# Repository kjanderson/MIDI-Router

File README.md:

# MIDI-Router
PIC24/FPGA code to route MIDI data on prototype hardware.

The objective of this project is to build a prototype that is able to route MIDI
signals from source to destination automatically.

The hardware provides 4 MIDI inputs, 4 MIDI thru's, and 4 MIDI outputs.
This software project implements the routing of the inputs to the outputs.

Notes
 - USB is copied from the MLA USB Framework
 - USB-app is copied from the application example in the MLA
 - USB-bsp is copied from the application example in the MLA

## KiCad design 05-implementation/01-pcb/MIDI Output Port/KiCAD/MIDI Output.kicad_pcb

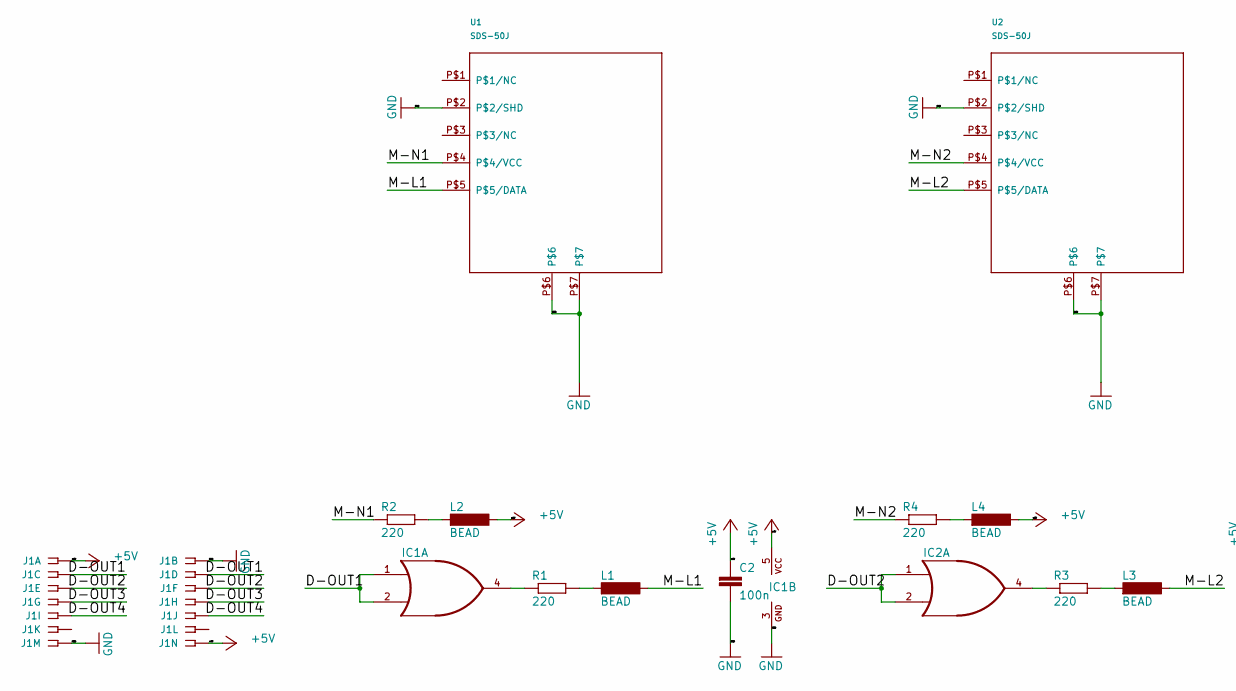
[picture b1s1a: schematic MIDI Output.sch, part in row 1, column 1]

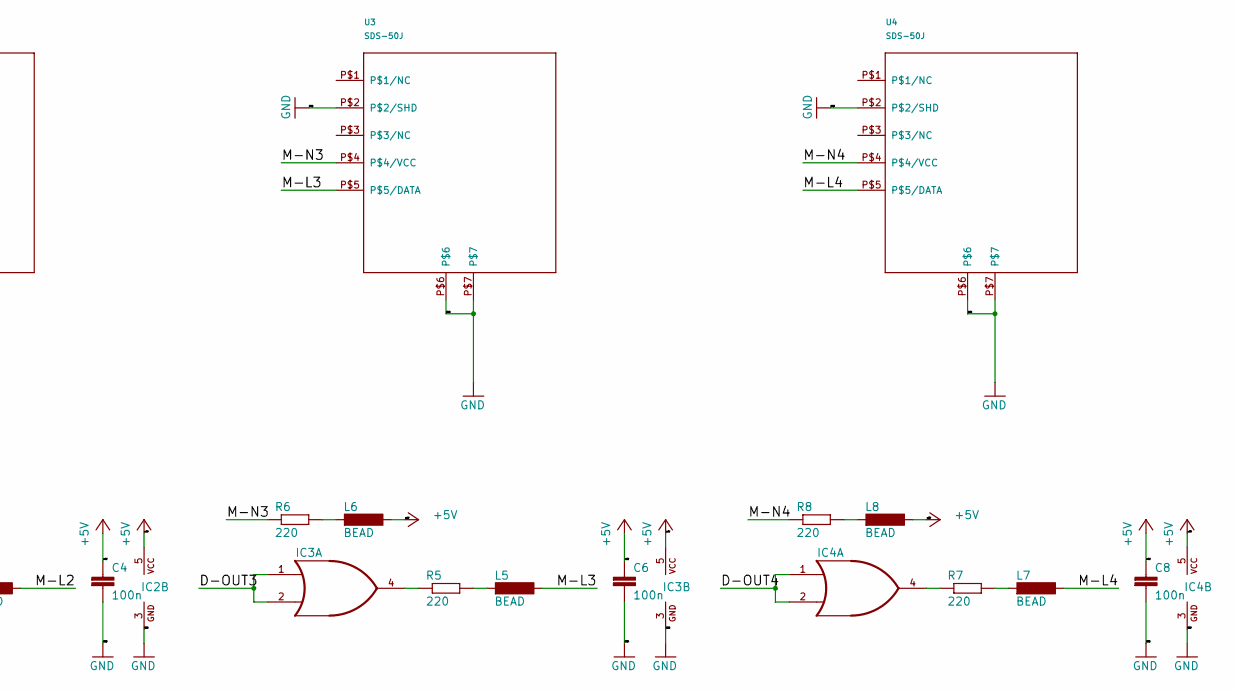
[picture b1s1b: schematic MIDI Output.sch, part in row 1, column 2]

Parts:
C2, C4, C6, C8: 100n; C0805
IC1, IC2, IC3, IC4: 741G32; SOT25
J1: SSW-107-02-G-D
L1, L2, L3, L4, L5, L6, L7, L8: BEAD; L0805
R1, R2, R3, R4, R5, R6, R7, R8: 220; R0805
U1, U2, U3, U4: SDS-50J

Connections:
+5V: C2.1, C4.1, C6.1, C8.1, IC1.5 (VCC), IC2.5 (VCC), IC3.5 (VCC), IC4.5 (VCC), J1.1, J1.14, L2.2, L4.2, L6.2, L8.2
/D-OUT1: IC1.1 (I0), IC1.2 (I1), J1.3, J1.4
/D-OUT2: IC2.1 (I0), IC2.2 (I1), J1.5, J1.6
/D-OUT3: IC3.1 (I0), IC3.2 (I1), J1.7, J1.8
/D-OUT4: IC4.1 (I0), IC4.2 (I1), J1.9, J1.10
/M-L1: L1.2, U1.P$5 (P$5/DATA)
/M-L2: L3.2, U2.P$5 (P$5/DATA)
/M-L3: L5.2, U3.P$5 (P$5/DATA)
/M-L4: L7.2, U4.P$5 (P$5/DATA)
/M-N1: R2.1, U1.P$4 (P$4/VCC)
/M-N2: R4.1, U2.P$4 (P$4/VCC)
/M-N3: R6.1, U3.P$4 (P$4/VCC)
/M-N4: R8.1, U4.P$4 (P$4/VCC)
GND: C2.2, C4.2, C6.2, C8.2, IC1.3 (GND), IC2.3 (GND), IC3.3 (GND), IC4.3 (GND), J1.2, J1.13, U1.P$2 (P$2/SHD), U1.P$6, U1.P$7, U2.P$2 (P$2/SHD), U2.P$6, U2.P$7, U3.P$2 (P$2/SHD), U3.P$6, U3.P$7, U4.P$2 (P$2/SHD), U4.P$6, U4.P$7
unnamed: IC1.4 (O), R1.1
unnamed: IC2.4 (O), R3.1
unnamed: IC3.4 (O), R5.1
unnamed: IC4.4 (O), R7.1
unnamed: L1.1, R1.2
unnamed: L2.1, R2.2
unnamed: L3.1, R3.2
unnamed: L4.1, R4.2
unnamed: L5.1, R5.2
unnamed: L6.1, R6.2
unnamed: L7.1, R7.2
unnamed: L8.1, R8.2

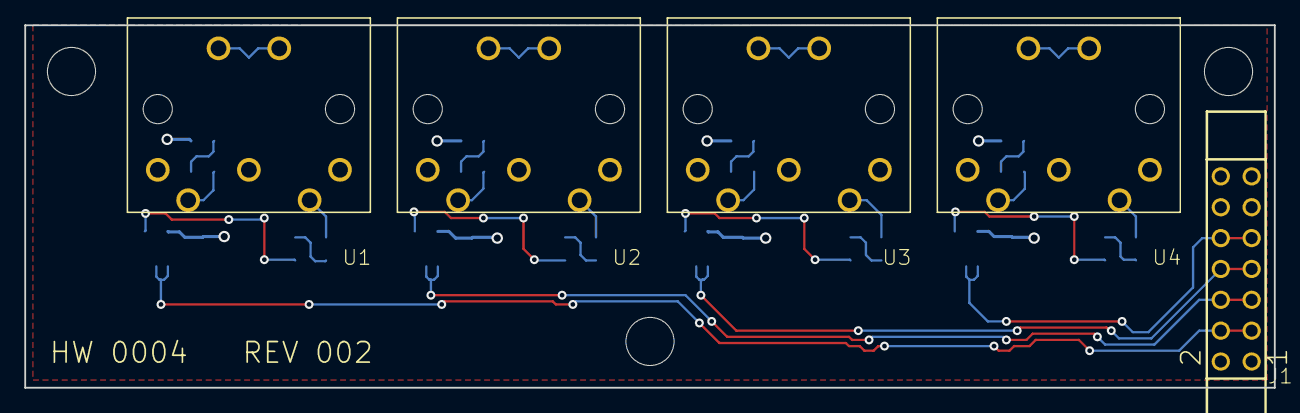
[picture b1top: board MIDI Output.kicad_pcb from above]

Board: 2 copper layers, 102.9 x 29.8 mm, 32 parts (0 on the bottom side), 26 nets.

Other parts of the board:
@HOLE0, @HOLE1, @HOLE2: (no value)

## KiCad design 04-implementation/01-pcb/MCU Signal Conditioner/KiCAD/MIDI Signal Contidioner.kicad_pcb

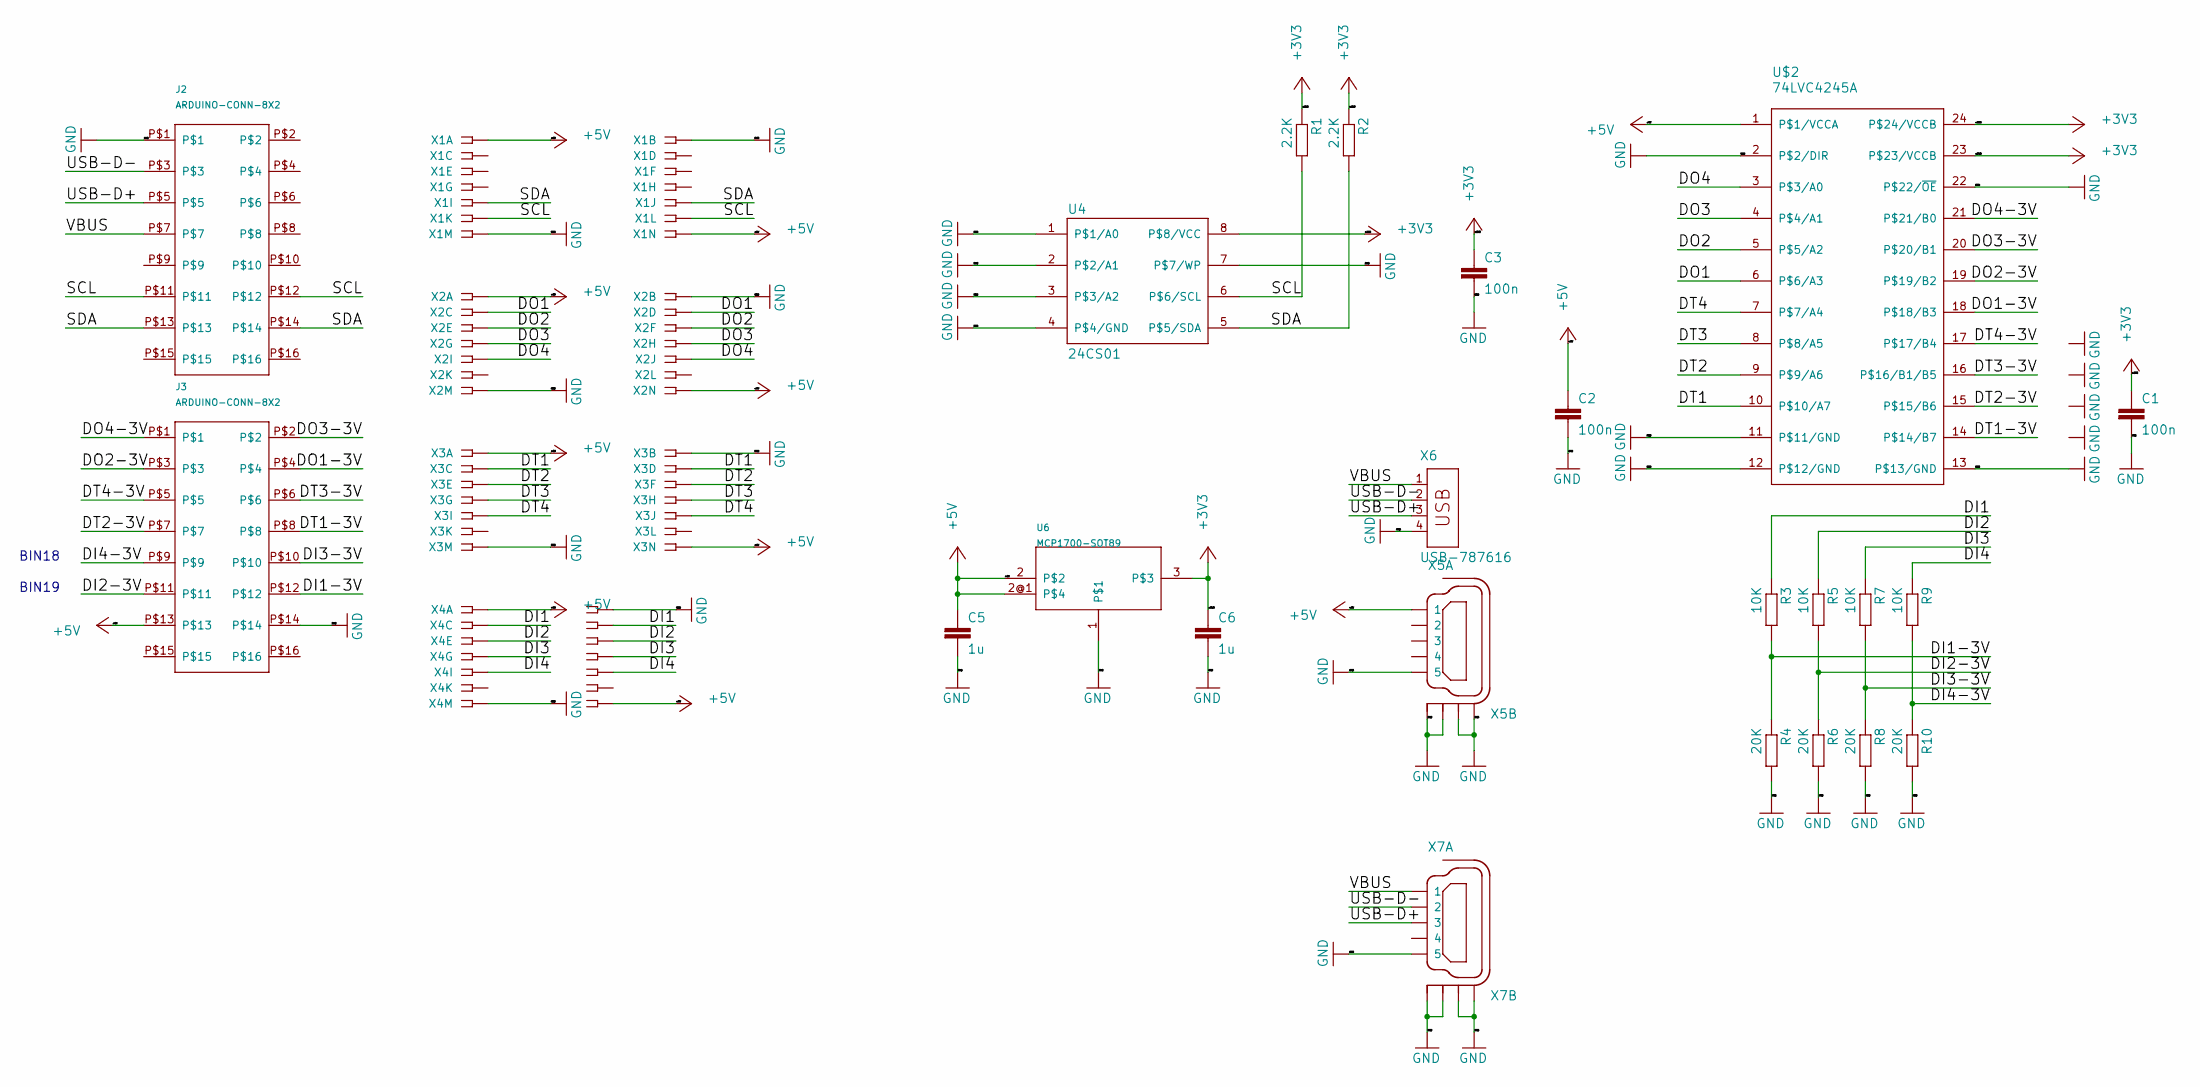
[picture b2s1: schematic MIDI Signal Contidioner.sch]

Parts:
C1, C2, C3: 100n; C0805
C5, C6: 1u; C0805
J2, J3: ARDUINO-CONN-8X2
R1, R2: 2.2K; R0805W
R3, R5, R7, R9: 10K; R0805W
R4, R6, R8, R10: 20K; R0805W
U4: 24CS01; 24CS01-SO8
U6: MCP1700-SOT89
U$2: 74LVC4245A; 74LVC4245A-SO24
X1, X2, X3, X4: SSW-107-02-G-D
X5, X7: MINI-USB-SHIELD-32005-201; MINI-USB-32005-201
X6: USB-787616; USB

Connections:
+3V3: C1.1, C3.1, C6.1, R1.1, R2.1, U4.8 (P$8/VCC), U6.3, U$2.23 (P$23/VCCB), U$2.24 (P$24/VCCB)
+5V: C2.1, C5.1, J3.P$13, U6.2, U6.2@1, U$2.1 (P$1/VCCA), X1.1, X1.14, X2.1, X2.14, X3.1, X3.14, X4.1, X4.14, X5.1
/DI1: R3.1, X4.3, X4.4
/DI1-3V: J3.P$12, R3.2, R4.1
/DI2: R5.1, X4.5, X4.6
/DI2-3V: J3.P$11, R5.2, R6.1
/DI3: R7.1, X4.7, X4.8
/DI3-3V: J3.P$10, R7.2, R8.1
/DI4: R9.1, X4.9, X4.10
/DI4-3V: J3.P$9, R9.2, R10.1
/DO1: U$2.6 (P$6/A3), X2.3, X2.4
/DO1-3V: J3.P$4, U$2.18 (P$18/B3)
/DO2: U$2.5 (P$5/A2), X2.5, X2.6
/DO2-3V: J3.P$3, U$2.19 (P$19/B2)
/DO3: U$2.4 (P$4/A1), X2.7, X2.8
/DO3-3V: J3.P$2, U$2.20 (P$20/B1)
/DO4: U$2.3 (P$3/A0), X2.9, X2.10
/DO4-3V: J3.P$1, U$2.21 (P$21/B0)
/DT1: U$2.10 (P$10/A7), X3.3, X3.4
/DT1-3V: J3.P$8, U$2.14 (P$14/B7)
/DT2: U$2.9 (P$9/A6), X3.5, X3.6
/DT2-3V: J3.P$7, U$2.15 (P$15/B6)
/DT3: U$2.8 (P$8/A5), X3.7, X3.8
/DT3-3V: J3.P$6, U$2.16 (P$16/B1/B5)
/DT4: U$2.7 (P$7/A4), X3.9, X3.10
/DT4-3V: J3.P$5, U$2.17 (P$17/B4)
/SCL: J2.P$11, J2.P$12, R1.2, U4.6 (P$6/SCL), X1.11, X1.12
/SDA: J2.P$13, J2.P$14, R2.2, U4.5 (P$5/SDA), X1.9, X1.10
/USB-D+: J2.P$5, X6.3, X7.3
/USB-D-: J2.P$3, X6.2, X7.2
/VBUS: J2.P$7, X6.1, X7.1
GND: C1.2, C2.2, C3.2, C5.2, C6.2, J2.P$1, J3.P$14, R4.2, R6.2, R8.2, R10.2, U4.1 (P$1/A0), U4.2 (P$2/A1), U4.3 (P$3/A2), U4.4 (P$4/GND), U4.7 (P$7/WP), U6.1, U$2.2 (P$2/DIR), U$2.11 (P$11/GND), U$2.12 (P$12/GND), U$2.13 (P$13/GND), U$2.22 (P$22/~OE), X1.2, X1.13, X2.2, X2.13, X3.2, X3.13, X4.2, X4.13, X5.5, X5.M1 (S1), X5.M2 (S2), X5.M3 (S3), X5.M4 (S4), X6.4, X7.5, X7.M1 (S1), X7.M2 (S2), X7.M3 (S3), X7.M4 (S4)

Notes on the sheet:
BIN18
BIN19

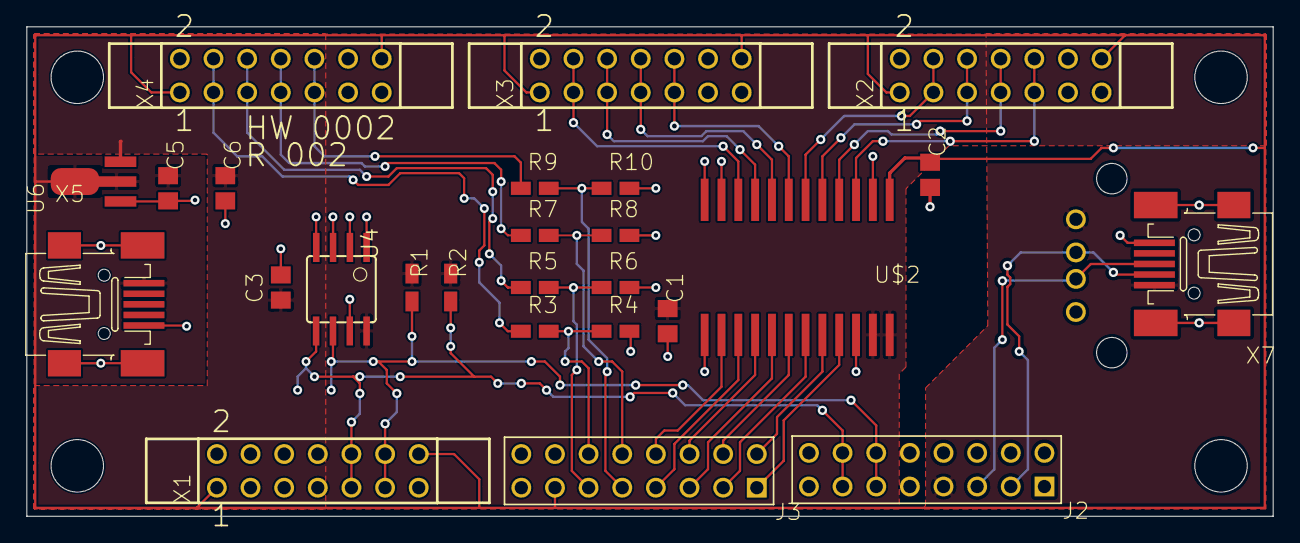
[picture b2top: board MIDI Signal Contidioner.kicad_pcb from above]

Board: 2 copper layers, 94.1 x 37.0 mm, 31 parts (0 on the bottom side), 32 nets.

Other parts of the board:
@HOLE0, @HOLE1, @HOLE2, @HOLE3: (no value)

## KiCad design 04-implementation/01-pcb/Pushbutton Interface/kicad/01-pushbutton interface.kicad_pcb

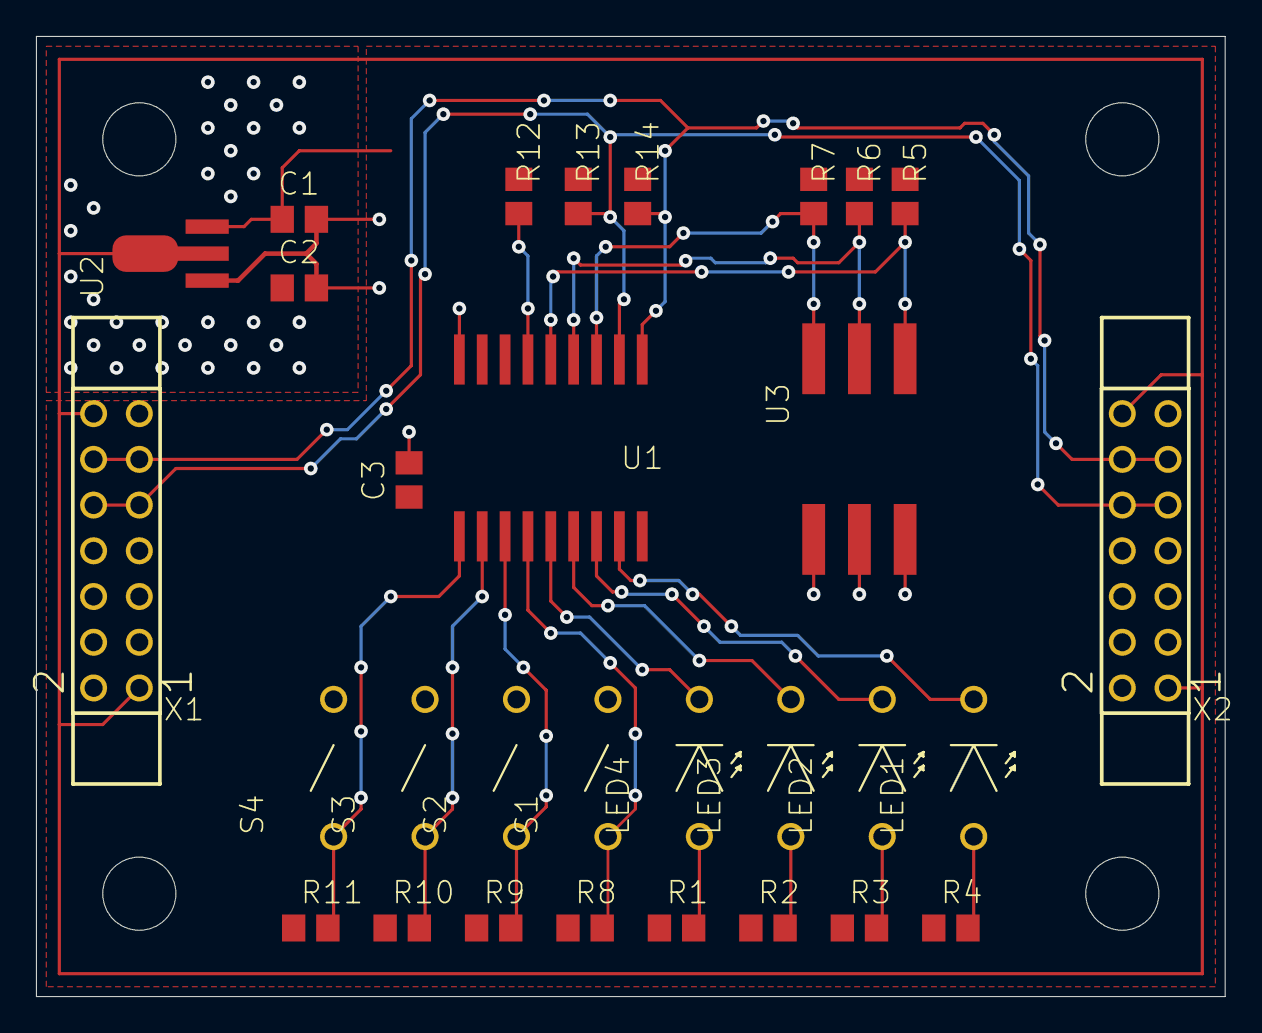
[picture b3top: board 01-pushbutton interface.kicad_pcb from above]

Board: 2 copper layers, 66.0 x 53.3 mm, 34 parts (0 on the bottom side), 21 nets.

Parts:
@HOLE0, @HOLE1, @HOLE2, @HOLE3: (no value)
C1, C2: 1u; C0805
C3: 100n; C0805
LED1, LED2, LED3, LED4: 559-XXX-007; LED
R1, R2, R3, R4: 100; R0805
R5, R6, R7, R8, R9, R10, R11, R12: 100K; R0805
R13, R14: 2.2K; R0805
S1, S2, S3, S4: PB-SWITCH; SWITCH
U1: MCP23008; MCP23008-SO18
U2: MCP1700-SOT89
U3: 219-3LPSTR
X1, X2: SSW-107-02-G-D

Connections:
+3V3: C1.1, C3.1, R1.1, R2.1, R3.1, R4.1, R5.1, R6.1, R7.1, R8.1, R9.1, R10.1, R11.1, R12.1, R13.1, R14.1, U1.18, U2.3
+5V: C2.1, U2.2, U2.2@1, X1.1, X1.14, X2.1, X2.14
/SCL: R14.2, U1.1, X1.11, X1.12, X2.11, X2.12
/SDA: R13.2, U1.2, X1.9, X1.10, X2.9, X2.10
GND: C1.2, C2.2, C3.2, S1.P$2, S2.P$2, S3.P$2, S4.P$2, U1.9, U2.1, U3.1, U3.2, U3.3, X1.2, X1.13, X2.2, X2.13
unnamed: LED1.P$1, R4.2
unnamed: LED1.P$2, U1.17
unnamed: LED2.P$1, R3.2
unnamed: LED2.P$2, U1.16
unnamed: LED3.P$1, R2.2
unnamed: LED3.P$2, U1.15
unnamed: LED4.P$1, R1.2
unnamed: LED4.P$2, U1.14
unnamed: R5.2, U1.5, U3.4
unnamed: R6.2, U1.4, U3.5
unnamed: R7.2, U1.3, U3.6
unnamed: R8.2, S1.P$1, U1.13
unnamed: R9.2, S2.P$1, U1.12
unnamed: R10.2, S3.P$1, U1.11
unnamed: R11.2, S4.P$1, U1.10
unnamed: R12.2, U1.6

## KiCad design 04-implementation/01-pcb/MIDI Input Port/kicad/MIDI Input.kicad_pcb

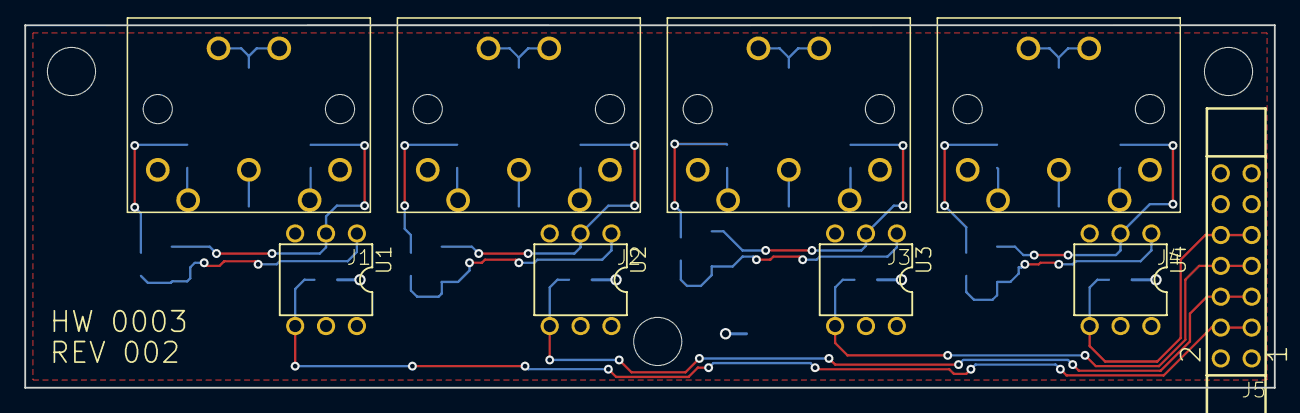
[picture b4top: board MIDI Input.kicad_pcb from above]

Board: 2 copper layers, 102.9 x 29.8 mm, 41 parts (0 on the bottom side), 34 nets.

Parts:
@HOLE0, @HOLE1, @HOLE2: (no value)
C1, C2, C3, C4, C5, C6, C7, C8, C9: 100n; C0805
D1, D2, D3, D4: 1N914; SOD323-W
J1, J2, J3, J4: SDS-50J
J5: SSW-107-02-G-D
L1, L2, L3, L4, L5, L6, L7, L8: BEAD; L0805
R1, R3, R5, R7: 220; R0805
R2, R4, R6, R8: 280; R0805
U1, U2, U3, U4: PC900V; DIL06

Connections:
+5V: C9.1, J5.1, J5.14, R2.2, R4.2, R6.2, R8.2, U1.P$6, U2.P$6, U3.P$6, U4.P$6
/D-IN1: J5.3, J5.4, R2.1, U1.P$4
/D-IN2: J5.5, J5.6, R4.1, U2.P$4
/D-IN3: J5.7, J5.8, R6.1, U3.P$4
/D-IN4: J5.9, J5.10, R8.1, U4.P$4
/M-L1: J1.P$5, L2.1
/M-L2: J2.P$5, L4.1
/M-L3: J3.P$5, L6.1
/M-L4: J4.P$5, L8.1
/M-N1: J1.P$4, R1.1
/M-N2: J2.P$4, R3.1
/M-N3: J3.P$4, R5.1
/M-N4: J4.P$4, R7.1
GND: C1.2, C2.2, C3.2, C4.2, C5.2, C6.2, C7.2, C8.2, C9.2, J5.2, J5.13, U1.P$5, U2.P$5, U3.P$5, U4.P$5
unnamed: C1.1, J1.P$2
unnamed: C2.1, J1.P$6, J1.P$7
unnamed: C3.1, J2.P$2
unnamed: C4.1, J2.P$6, J2.P$7
unnamed: C5.1, J3.P$2
unnamed: C6.1, J3.P$6, J3.P$7
unnamed: C7.1, J4.P$2
unnamed: C8.1, J4.P$6, J4.P$7
unnamed: D1.A, L2.2, U1.P$2
unnamed: D1.C, L1.2, U1.P$1
unnamed: D2.A, L4.2, U2.P$2
unnamed: D2.C, L3.2, U2.P$1
unnamed: D3.A, L6.2, U3.P$2
unnamed: D3.C, L5.2, U3.P$1
unnamed: D4.A, L8.2, U4.P$2
unnamed: D4.C, L7.2, U4.P$1
unnamed: L1.1, R1.2
unnamed: L3.1, R3.2
unnamed: L5.1, R5.2
unnamed: L7.1, R7.2

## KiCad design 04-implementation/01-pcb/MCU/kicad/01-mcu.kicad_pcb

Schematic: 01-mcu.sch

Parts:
C1, C3, C4, C5, C7, C9, C11, C13, C15, C21, C23, C25: 100n; C0805
C6: 10u; C0805
C8, C10, C12, C14, C16, C22, C24, C26: 10n; C0805
C17, C18, C19, C20: 1u; C0805
D2: MBR0520; MBR0520-SOD-123_MINI-SMA
IC1: PIC24FJ128GB204; TQFP44
J2, J3: ARDUINO-CONN-8X2
J4: ARDUINO-CONN-8
J6: ARDUINO-CONN-6
J7: PICKIT-ICSP
L1, L2: BEAD; L0805
LED1, LED3: LEDCHIP-LED0805; CHIP-LED0805
R1, R3: 100; R0805
R2, R4, R5, R6: 10K; R0805
R7, R9: 680; R0805
R8: 10; R0805
U2: ICE40-HX1K-VQFP100; TQFP100-14X14
U3: SP0502BAHT-SOT23; SOT23
U101: MCP1700-1202E_SOT89; SOT-89-3_Handsoldering
U102: MCP1700-3302E_SOT89; SOT-89-3_Handsoldering

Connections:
+5V: C17.1, J3.P$14, J4.P$5, U102.2 (VI)
/AN0: IC1.26, J6.P$1
/AN1: IC1.25, J6.P$2
/AN2: IC1.24, J6.P$3
/AN3: IC1.23, J6.P$4
/AN4: IC1.22, J6.P$5
/AN5: IC1.21, J6.P$6
/AVDD: C4.1, IC1.17, L1.2, L2.2
/BIN8: J3.P$1, U2.26
/BIN9: J3.P$3, U2.28
/BIN10: J3.P$5, U2.30
/BIN11: J3.P$7, U2.34
/BIN12: J3.P$9, U2.37
/BIN13: J3.P$11, U2.41
/BIN14: J3.P$2, U2.27
/BIN15: J3.P$4, U2.29
/BIN16: J3.P$6, U2.33
/BIN17: J3.P$8, U2.36
/BIN18: J3.P$10, U2.40
/BIN19: J3.P$12, U2.42
/CDONE: IC1.35, R4.2, U2.43
/CRESET: IC1.34, R5.2, U2.44
/FBIN0: IC1.1, U2.19
/FBIN1: IC1.2, U2.18
/FBIN2: IC1.3, U2.16
/FBIN3: IC1.4, U2.15
/MISO: IC1.43, U2.45
/MODE: IC1.33, R9.1
/MOSI: IC1.38, U2.46
/PGC: IC1.20, J7.P$5
/PGD: IC1.19, J7.P$4
/REFO: R8.1, U2.13
/SCK: IC1.37, U2.48
/USB-D+: IC1.8, J2.P$6, U3.3
/USB-D-: IC1.9, J2.P$4, U3.2
/VBUS: J2.P$8, R3.2
/~MCLR: C5.1, J7.P$1, R1.1, R2.1
/~SS: IC1.36, R6.2, U2.49
GND: C1.2, C3.2, C4.2, C5.2, C6.1, C7.2, C8.2, C9.2, C10.2, C11.2, C12.2, C13.2, C14.2, C15.2, C16.2, C17.2, C18.2, C19.2, C20.2, C21.2, C22.2, C23.2, C24.2, C25.2, C26.2, IC1.16, IC1.29, IC1.39, J2.P$2, J3.P$13, J4.P$6, J4.P$7, J7.P$3, R6.1, R7.1, U2.5, U2.17, U2.23, U2.32, U2.39, U2.47, U2.55, U2.70, U2.84, U2.98, U3.1, U101.1 (GND), U102.1 (GND)
unnamed: C6.2, IC1.7
unnamed: D2.C, U2.75
unnamed: IC1.11, R8.2
unnamed: IC1.18, R1.2
unnamed: IC1.42, R3.1
unnamed: LED1.C, R7.2
unnamed: LED3.C, R9.2
VCCINT: C15.1, C16.1, C19.1, C21.1, C22.1, C23.1, C24.1, C25.1, C26.1, U2.11, U2.35, U2.61, U2.77, U101.3 (VO)
VDD: C1.1, C3.1, C7.1, C8.1, C9.1, C10.1, C11.1, C12.1, C13.1, C14.1, C18.1, C20.1, D2.A, IC1.10, IC1.28, IC1.40, J4.P$4, J7.P$2, L1.1, L2.1, LED1.A, LED3.A, R2.2, R4.1, R5.1, U2.6, U2.14, U2.22, U2.31, U2.38, U2.50, U2.58, U2.67, U2.88, U2.92, U101.2 (VI), U102.3 (VO)

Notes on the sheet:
3.3V
5.0V
GND
AREF
BIN0
BIN1
BIN2
BIN3
BIN4
BIN5
BIN6
BIN7
USB-D-
USB-D+
VBUS
BIN12
BIN13
BIN14
BIN15
BIN8
BIN9
BIN10
BIN11
SCL
SDA
BIN16
BIN17
BIN18
BIN19
BIN20
BIN21

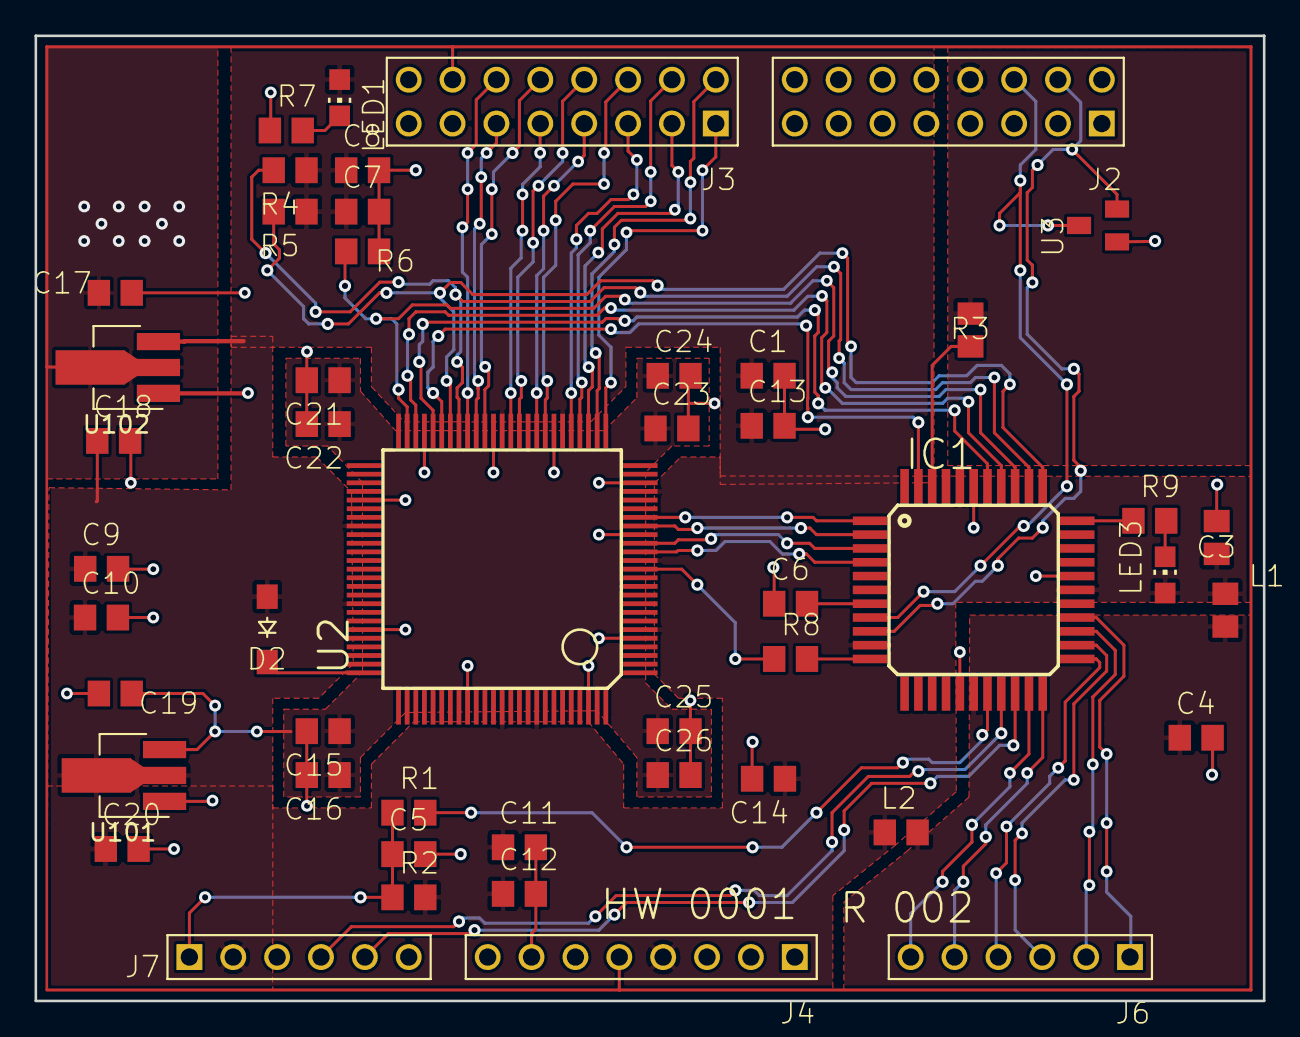
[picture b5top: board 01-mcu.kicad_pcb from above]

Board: 2 copper layers, 71.1 x 55.9 mm, 49 parts (0 on the bottom side), 48 nets.

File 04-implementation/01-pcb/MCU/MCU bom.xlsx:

Part | Value | Device | Package | Description | RATING | SPICEPREFIX
C1 | 100n | C-EUC0805 | C0805 | CAPACITOR, European symbol |  | C
C3 | 100n | C-EUC0805 | C0805 | CAPACITOR, European symbol |  | C
C4 | 100n | C-EUC0805 | C0805 | CAPACITOR, European symbol |  | C
C5 | 100n | C-EUC0805 | C0805 | CAPACITOR, European symbol |  | C
C6 | 10u | C-EUC0805 | C0805 | CAPACITOR, European symbol | 6.3V | C
C7 | 100n | C-EUC0805 | C0805 | CAPACITOR, European symbol |  | C
C8 | 10n | C-EUC0805 | C0805 | CAPACITOR, European symbol |  | C
C9 | 100n | C-EUC0805 | C0805 | CAPACITOR, European symbol |  | C
C10 | 10n | C-EUC0805 | C0805 | CAPACITOR, European symbol |  | C
C11 | 100n | C-EUC0805 | C0805 | CAPACITOR, European symbol |  | C
C12 | 10n | C-EUC0805 | C0805 | CAPACITOR, European symbol |  | C
C13 | 100n | C-EUC0805 | C0805 | CAPACITOR, European symbol |  | C
C14 | 10n | C-EUC0805 | C0805 | CAPACITOR, European symbol |  | C
C15 | 100n | C-EUC0805 | C0805 | CAPACITOR, European symbol |  | C
C16 | 10n | C-EUC0805 | C0805 | CAPACITOR, European symbol |  | C
C17 | 1u | C-EUC0805 | C0805 | CAPACITOR, European symbol |  | C
C18 | 1u | C-EUC0805 | C0805 | CAPACITOR, European symbol |  | C
C19 | 1u | C-EUC0805 | C0805 | CAPACITOR, European symbol |  | C
C20 | 1u | C-EUC0805 | C0805 | CAPACITOR, European symbol |  | C
C21 | 100n | C-EUC0805 | C0805 | CAPACITOR, European symbol |  | C
C22 | 10n | C-EUC0805 | C0805 | CAPACITOR, European symbol |  | C
C23 | 100n | C-EUC0805 | C0805 | CAPACITOR, European symbol |  | C
C24 | 10n | C-EUC0805 | C0805 | CAPACITOR, European symbol |  | C
C25 | 100n | C-EUC0805 | C0805 | CAPACITOR, European symbol |  | C
C26 | 10n | C-EUC0805 | C0805 | CAPACITOR, European symbol |  | C
D2 | MBR0520 | MBR0520 | MBR0520-SOD-123_MINI-SMA
IC1 | PIC24FJ128GB204 | PIC24FJ128GB204 | TQFP44 | PIC24FJ64GA00416-bit microcontroller
J2 | ARDUINO-CONN-8X2 | ARDUINO-CONN-8X2 | ARDUINO-CONN-8X2
J3 | ARDUINO-CONN-8X2 | ARDUINO-CONN-8X2 | ARDUINO-CONN-8X2
J4 | ARDUINO-CONN-8 | ARDUINO-CONN-8 | ARDUINO-CONN-8
J6 | ARDUINO-CONN-6 | ARDUINO-CONN-6 | ARDUINO-CONN-6
J7 | PICKIT-ICSP | PICKIT-ICSP | PICKIT-ICSP
L1 | BEAD | BEAD | L0805
L2 | BEAD | BEAD | L0805
LED1 |  | LEDCHIP-LED0805 | CHIP-LED0805 | LED
LED3 |  | LEDCHIP-LED0805 | CHIP-LED0805 | LED
R1 | 100 | R-EU_R0805 | R0805 | RESISTOR, European symbol
R2 | 10K | R-EU_R0805 | R0805 | RESISTOR, European symbol
R3 | 100 | R-EU_R0805 | R0805 | RESISTOR, European symbol
R4 | 10K | R-EU_R0805 | R0805 | RESISTOR, European symbol
R5 | 10K | R-EU_R0805 | R0805 | RESISTOR, European symbol
R6 | 10K | R-EU_R0805 | R0805 | RESISTOR, European symbol
R7 | 680 | R-EU_R0805 | R0805 | RESISTOR, European symbol
R8 | 10 | R-EU_R0805 | R0805 | RESISTOR, European symbol
R9 | 680 | R-EU_R0805 | R0805 | RESISTOR, European symbol
U2 | ICE40-HX1K-VQFP100 | ICE40-HX1K-VQFP100 | TQFP100-14X14
U3 | SP0502BAHT-SOT23 | SP0502BAHT-SOT23 | SOT23
U4 | MCP1700-SOT89 | MCP1700-SOT89 | MCP1700-SOT89
U6 | MCP1700-SOT89 | MCP1700-SOT89 | MCP1700-SOT89

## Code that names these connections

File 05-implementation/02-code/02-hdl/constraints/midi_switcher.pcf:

# ##############################################################################

# iCEcube PCF

# Version:            2017.08.27940

# File Generated:     Feb 17 2018 06:34:16

# Family & Device:    iCE40HX1K

# Package:            VQ100

# ##############################################################################

###IOSet List 43
set_io clk 13
set_io gpio_fbin0 19
set_io gpio_fbin1 18
set_io gpio_fbin2 16
set_io gpio_fbin3 15
#set_io gpio_bin[0] 21
#set_io gpio_bin[1] 20
#set_io gpio_bin[2] 19
#set_io gpio_bin[3] 18
#set_io gpio_bin[0] 20
#set_io gpio_bin[1] 21
#set_io gpio_bin[2] 24
#set_io gpio_bin[3] 25
set_io midi_out[0] 26
set_io midi_out[2] 28
set_io midi_in[2] 30
set_io midi_in[0] 34
#set_io gpio_bin[8] 37
#set_io gpio_bin[9] 41
set_io midi_out[1] 27
set_io midi_out[3] 29
set_io midi_in[3] 33
set_io midi_in[1] 36
#set_io gpio_bin[14] 40
#set_io gpio_bin[15] 42
set_io spi_clk 48
set_io spi_miso 45
set_io spi_mosi 46
set_io spi_ss 49

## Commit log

2018-04-06 Add prototype implementation source code.
    Add files to help in board bring-up testing.
    Add file for power-on reset on Lattice parts.
    Add FPGA files to assist in testing connectivity between MCU and FPGA.
    Add basic shift register implementation.
    Add constraint files for timing and pin placement.
    Add bare-bones MCU test code.
2018-04-06 Modify HDL placement constraint file to be consistent with Rev 2 hardware. Add .gitignore to ignore MacOS .DS_Store files.
2018-04-06 Update README.md with a high-level description of the software.
2018-04-07 Add requirements analysis.
2018-04-07 Add files for PCB.
2018-04-07 Add files for USB project.
2018-04-07 Add support for version 2 hardware in HAL.
2018-04-07 Update FPGA startup sequence for HX1K device.
2018-04-08 Add application files to project.
2018-04-10 Add support for 1-msec timer. Add application logic for LED.
2018-04-10 Add system diagram to requirements analysis.
2018-04-11 Change signal conditioner board to 3.3V rail.
2018-04-11 Add schematic and pcb backup files to ignore list.
2018-04-12 Update signal conditioner.
2018-04-12 Begin placement of components. Add Eagle exclusion to .gitignore.
    Begin placement of components on board to reduce board area.
    Add exclusion rules for Eagle to .gitignore.
2018-04-12 Complete initial placement of components.
2018-04-12 Add comment block to _Hal_InitGpio().
2018-04-14 Update requirements analysis. Complete first pass at signal conditioner board. Add power analysis.
2018-04-14 Add code in hal.c to enable SPI1 and REFO.
2018-04-14 Add support for Timer1. Add guard conditions in FPGA configuration.
2018-04-16 Add comments to hal.c. Add application code to echo UART bytes.
2018-04-17 Add support for interrupts.
2018-04-17 Add SPI interrupt function to Hal.h. Update configuration bits.
2018-04-17 Repair defects in midi_switcher and shiftreg modules.
2018-04-18 Disable deep-sleep watchdog in configuration bits.
2018-04-19 Update configuration bits.
2018-04-20 Update configuration bits. Add support for software-controlled watchdog timer.
2018-04-23 Add net analysis for critical nets in system.
2018-04-24 Complete initial placement of signal conditioning board (5V).
2018-04-24 Add connector analysis spreadsheet.
2018-04-25 Update signal conditioner board.
2018-04-25 Update placement of signal conditioner footprints.
2018-04-26 Complete layout of signal conditioner board.
2018-04-26 Add system drawing.
2018-04-26 Trying quotes on picture.
2018-04-26 Trying full URL for system diagram.
2018-04-26 Removing link to system diagram in README.md.
2018-05-03 Update footprint for regulator on signal conditioner board.
2018-05-12 Add files to release PCB after successful board bring up.
2018-05-13 Add problem reports for PCB bringup. Add code to correct reported problems on HW0001 R002.
2018-07-04 Update test logs from Logic Interface Board PCB bringup.
2018-09-02 Add files for PCB bringup.
    Update FPGA image with 3.3V I/O logic (counter bound to I/O pins).
2018-09-03 Revise MIDI PCB's for mechanical spacing of ribbon connector.
2018-09-06 Add HDL code for application.
2018-11-13 Add L2 requirements. Add FPGA concept drawing.
2019-02-13 Update application with USB CDC and FPGA test state machine.
2019-02-13 Add project files for Icestorm toolchain.
2019-02-18 Add files for transition to KiCAD.
2019-02-23 Update to MPLAB-X 5.10.
2019-04-07 Add files for PCB releases.
2019-04-12 Add files for initial placement of pushbutton interface.
2019-04-14 Add files for pushbutton PCB.
2019-07-01 Archive Eagle design files and import to KiCAD.
2019-07-01 Finish moving eagle design.
2019-07-02 Convert MIDI Output board to KiCAD.
2019-08-22 Add outline for mechanical front panel
2019-08-24 Add template for flash event loop.
2019-10-09 Update requirements
2019-10-10 Add experimental code to test section assignment. Add systemverilog testbench for SPI module.
2019-10-11 Add to clocking block in SV testbench for shiftreg.
2019-10-12 Add clocking block I/O to interface in tb_sr.sv.
2019-10-17 Update testbench for shiftreg.
2019-10-18 Update hal.h.
2019-10-18 Incremental update to shiftreg testbench.
2019-10-19 Update shiftreg testbench so that it compiles.
2019-11-23 Add FBIN output ports to FPGA firmware for testing.
2019-11-23 Add files for test MCU image.
2019-11-29 Add files to test board bringup.
2019-12-01 Add unit tests for event-queue.
2019-12-01 Add queue code in preparation for unit tests.
2019-12-02 Add SPI interface file structure.
2019-12-21 Repair defect in SPI controller logic.
2019-12-23 Import pushbutton project to KiCAD.
2019-12-23 Add unit tests for SPI controller. Update SPI interrupt setup.
2019-12-23 Update fpga-icestorm makefile. Add SPI logic to timer ISR.
2019-12-25 Repair defect in SPI interrupt configuration. Add support for updates in unit tests.
2019-12-26 Update PCB for pushbutton PCB to fill copper pours.
2020-01-01 Add SPI controller implementation.
2020-01-02 Update SPI controller module in HDL code.
2020-01-02 Add KiCAD import of MCU Signal Conditioner
2020-01-03 Verified board-to-board pinouts are consistent.
2020-01-06 Update MCU Signal Conditioner PCB for placement compatibility with MCU PCB.
2020-02-15 Add files to verify 8 MHz clock from CPU to FPGA with minimal skew.
2020-02-16 Add synchronizer to design to synchronize MIDI inputs.
2020-02-17 Update FPGA image with synchronizers in the MCU firmware.
2020-03-01 Add midi output module.
2020-03-24 Add feature to register outputs for the MIDI merge HDL module.
2020-03-25 Repair defects in merge function.
2020-03-28 Add module fifo.v for output buffering.
2020-03-28 Add design drawing for HDL code.
2020-04-18 Add MIDI receiver implementation.
2020-10-05 Update source files to fix unsynchronized inputs.
2020-11-14 Update working copy.
2020-12-24 Updating files for desktop OS transfer.
2021-01-01 Add files to support simulation of SPI state machine.
2021-02-15 Update for lscc test.
2021-09-06 Add files for version 1.0.
2021-09-06 Add files and tags for 1.0 releases.
